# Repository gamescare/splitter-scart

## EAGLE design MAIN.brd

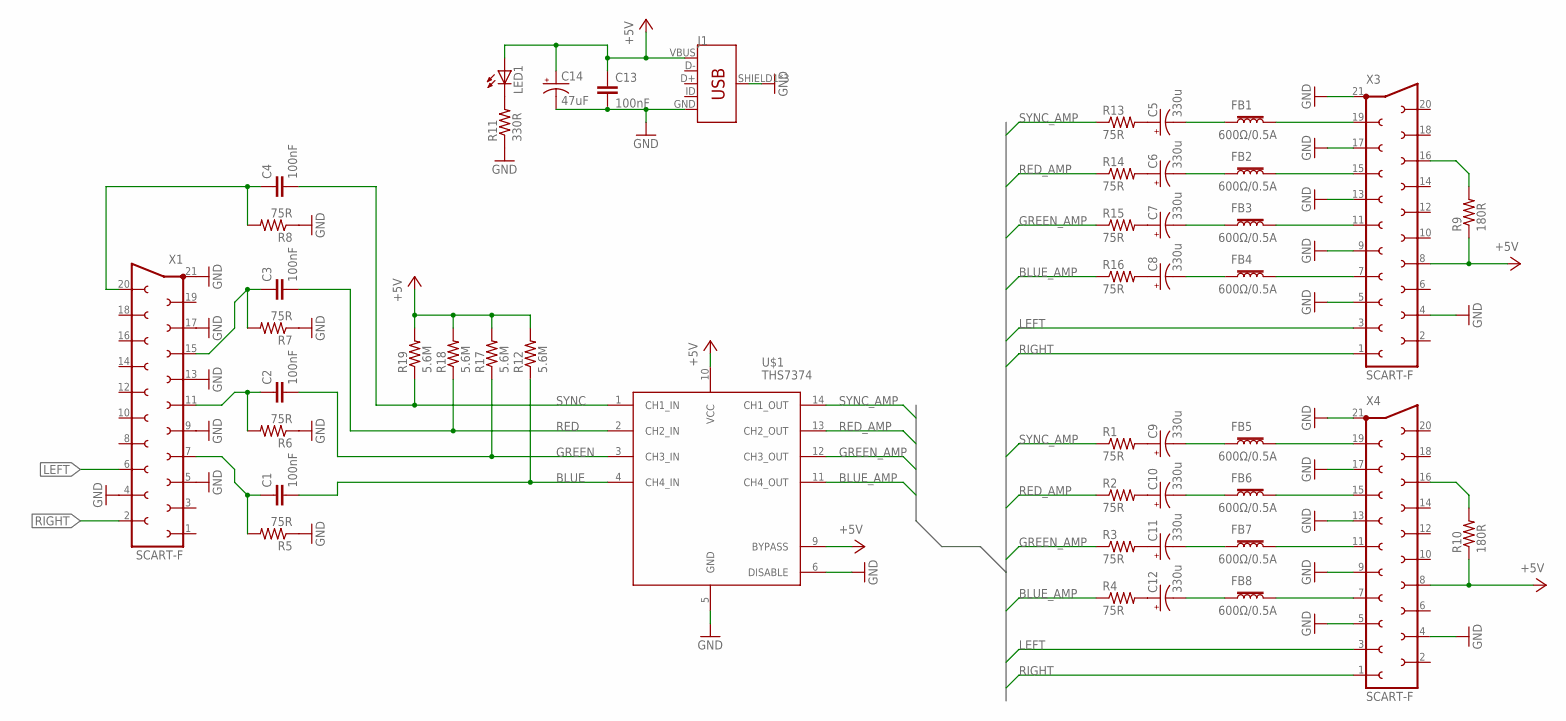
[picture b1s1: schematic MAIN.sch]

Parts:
C1, C2, C3, C4, C13: 100nF; C050-025X075
C5, C6, C7, C8, C9, C10, C11, C12: 330u; E3,5-8
C14: 47uF; E3,5-8
FB1, FB2, FB3, FB4, FB5, FB6, FB7, FB8: 600Ω/0.5A; 0603
J1: USB_MICRO-B_FEMALE-SMT; USB-B-MICRO-SMD
LED1: LED5MM
R1, R2, R3, R4, R5, R6, R7, R8, R13, R14, R15, R16: 75R; 0204/7
R9, R10: 180R; 0204/7
R11: 330R; 0204/7
R12, R17, R18, R19: 5.6M; 0204/7
U$1: THS7374; TSSOP-14
X1, X3, X4: SCART-F

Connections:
+5V: C13.1, C14.+, J1.VBUS, LED1.A, R9.1, R10.1, R12.2, R17.2, R18.2, R19.2, U$1.9 (BYPASS), U$1.10 (VCC), X3.8, X4.8
BLUE: C1.2, R12.1, U$1.4 (CH4_IN)
BLUE_AMP: R4.1, R16.1, U$1.11 (CH4_OUT)
GND: C13.2, C14.-, J1.GND, J1.SHIELD1 (SHIELD), J1.SHIELD2 (SHIELD), J1.SHIELD3 (SHIELD), R5.1, R6.1, R7.1, R8.1, R11.1, U$1.5 (GND), U$1.6 (DISABLE), X1.4, X1.5, X1.9, X1.13, X1.17, X1.21, X3.4, X3.5, X3.9, X3.13, X3.17, X3.21, X4.4, X4.5, X4.9, X4.13, X4.17, X4.21
GREEN: C2.2, R17.1, U$1.3 (CH3_IN)
GREEN_AMP: R3.1, R15.1, U$1.12 (CH3_OUT)
LEFT: X1.6, X3.3, X4.3
unnamed: C9.+, R1.2
unnamed: C10.+, R2.2
unnamed: C11.+, R3.2
unnamed: C12.+, R4.2
unnamed: C5.+, R13.2
unnamed: C6.+, R14.2
unnamed: C7.+, R15.2
unnamed: C8.+, R16.2
unnamed: R10.2, X4.16
unnamed: C1.1, R5.2, X1.7
unnamed: R9.2, X3.16
unnamed: C2.1, R6.2, X1.11
unnamed: C3.1, R7.2, X1.15
unnamed: LED1.K (C), R11.2
unnamed: C4.1, R8.2, X1.20
unnamed: C5.-, FB1.1
unnamed: C6.-, FB2.1
unnamed: C7.-, FB3.1
unnamed: C8.-, FB4.1
unnamed: FB1.2, X3.19
unnamed: FB2.2, X3.15
unnamed: FB3.2, X3.11
unnamed: FB4.2, X3.7
unnamed: FB8.2, X4.7
unnamed: FB7.2, X4.11
unnamed: FB6.2, X4.15
unnamed: FB5.2, X4.19
unnamed: C9.-, FB5.1
unnamed: C10.-, FB6.1
unnamed: C11.-, FB7.1
unnamed: C12.-, FB8.1
RED: C3.2, R18.1, U$1.2 (CH2_IN)
RED_AMP: R2.1, R14.1, U$1.13 (CH2_OUT)
RIGHT: X1.2, X3.1, X4.1
SYNC: C4.2, R19.1, U$1.1 (CH1_IN)
SYNC_AMP: R1.1, R13.1, U$1.14 (CH1_OUT)

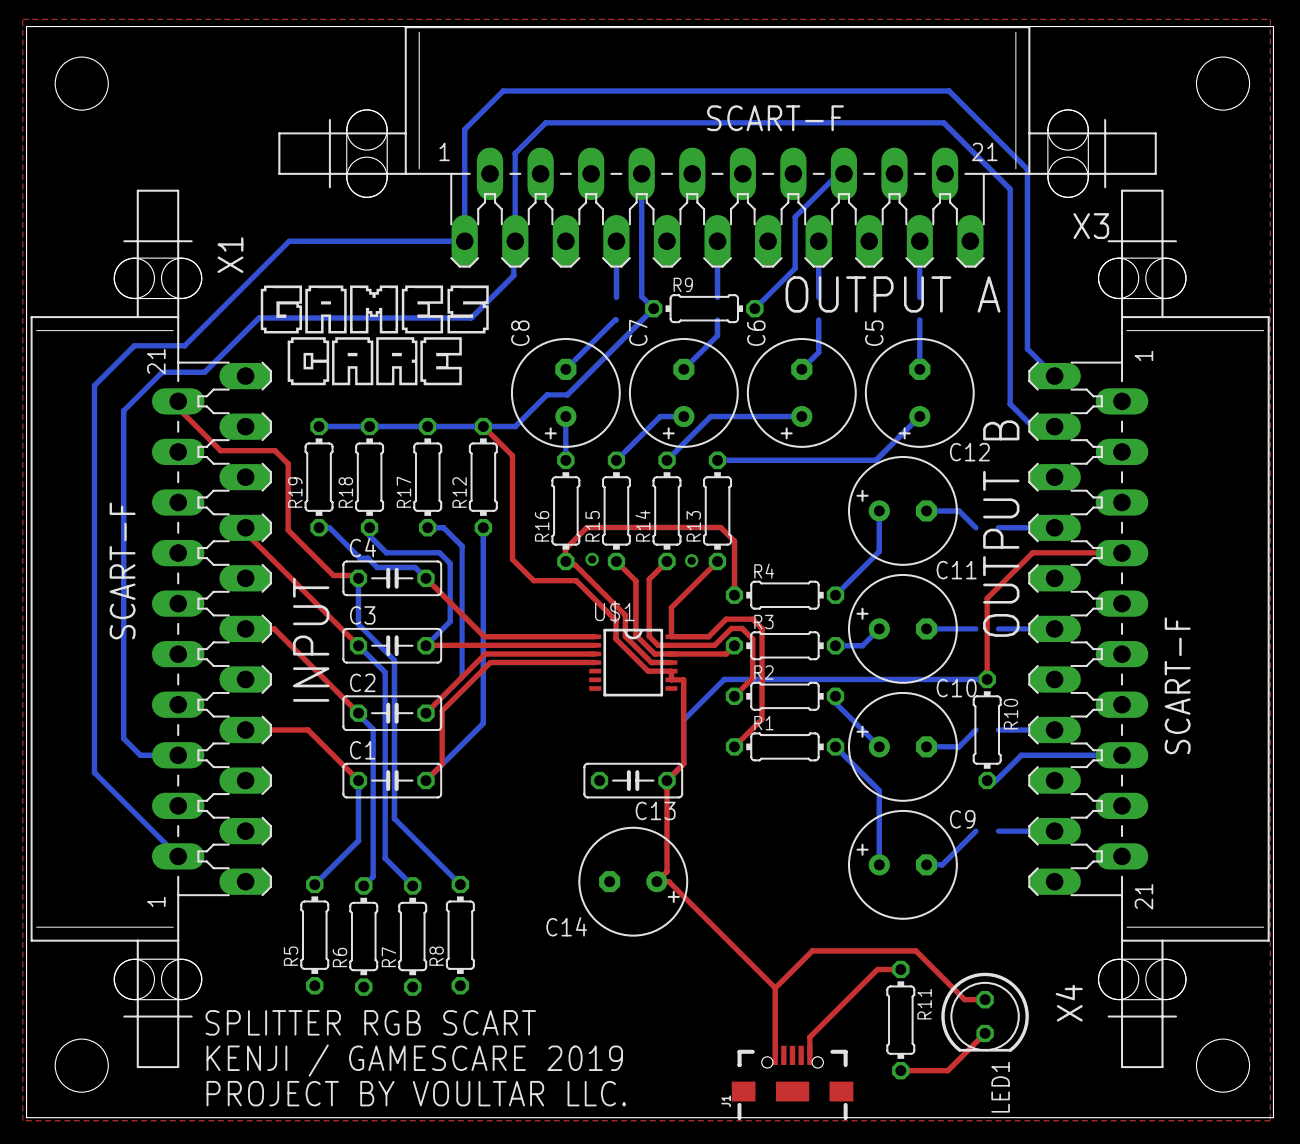
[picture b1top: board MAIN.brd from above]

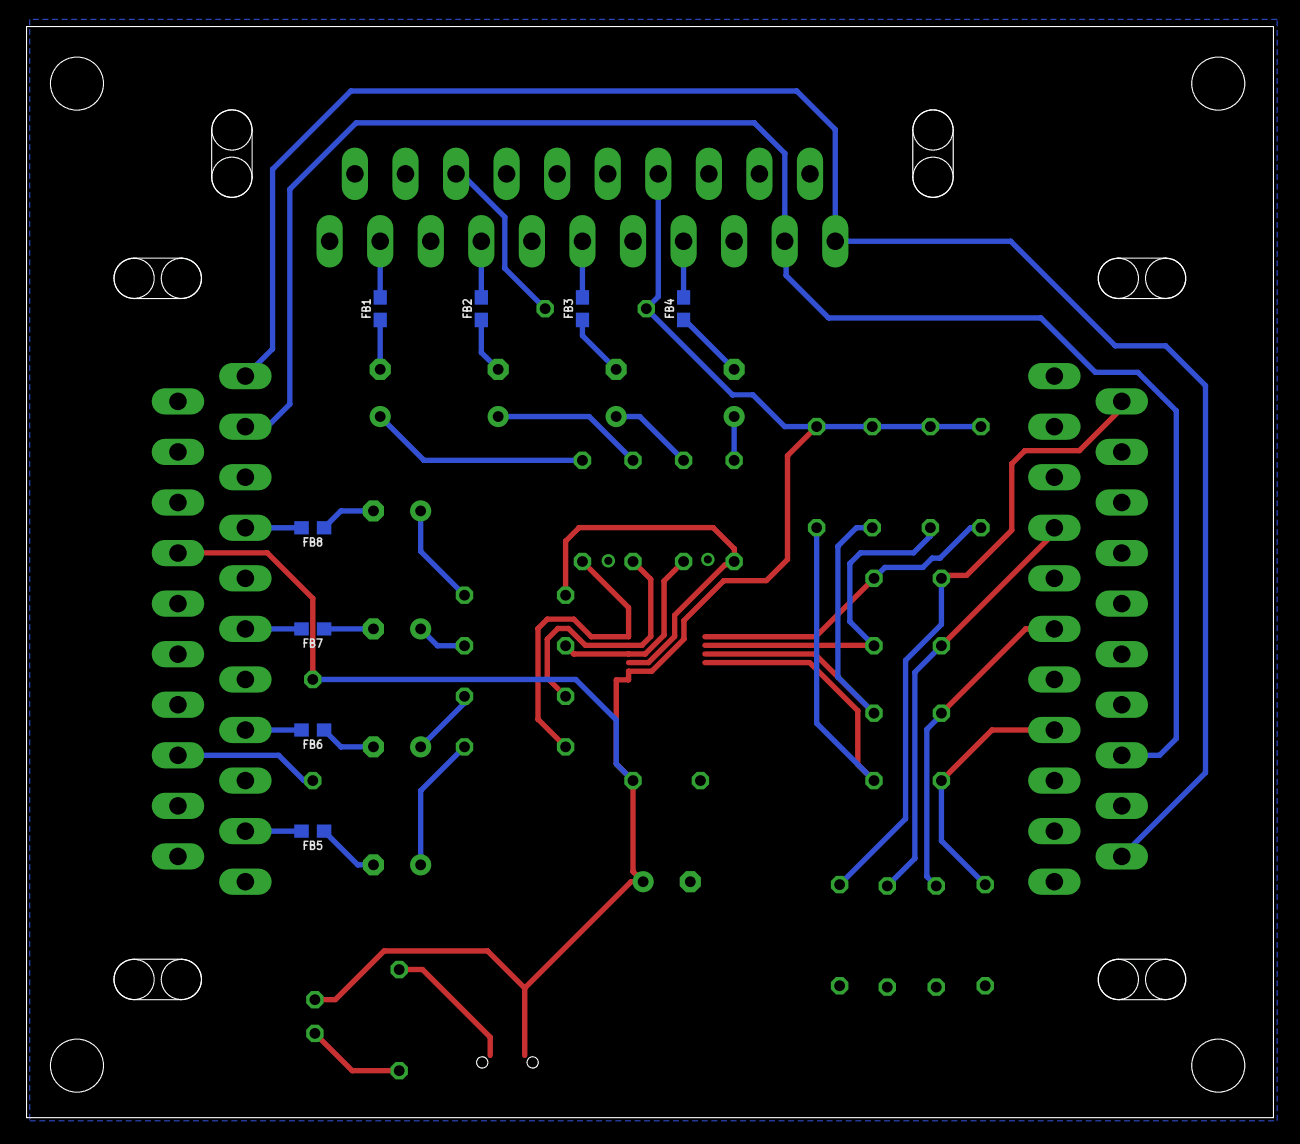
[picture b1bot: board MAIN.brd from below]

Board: 2 copper layers, 94.0 x 82.2 mm, 47 parts (8 on the bottom side), 43 nets.

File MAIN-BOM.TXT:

Partlist exported from C:/Users/eduar/Documents/eagle/SCART SPLITTER/SCART - 2X SCART/MAIN.sch at 29/05/2019 15:09

Part Value          Device            Package      Description                                       MF MPN OC_FARNELL OC_NEWARK PROD_ID    SF_ID     VALUE   
C1   100nF          C-EU050-025X075   C050-025X075 CAPACITOR, European symbol                                                                                 
C2   100nF          C-EU050-025X075   C050-025X075 CAPACITOR, European symbol                                                                                 
C3   100nF          C-EU050-025X075   C050-025X075 CAPACITOR, European symbol                                                                                 
C4   100nF          C-EU050-025X075   C050-025X075 CAPACITOR, European symbol                                                                                 
C5   330u           CPOL-USE3.5-8     E3,5-8       POLARIZED CAPACITOR, American symbol                                                                       
C6   330u           CPOL-USE3.5-8     E3,5-8       POLARIZED CAPACITOR, American symbol                                                                       
C7   330u           CPOL-USE3.5-8     E3,5-8       POLARIZED CAPACITOR, American symbol                                                                       
C8   330u           CPOL-USE3.5-8     E3,5-8       POLARIZED CAPACITOR, American symbol                                                                       
C9   330u           CPOL-USE3.5-8     E3,5-8       POLARIZED CAPACITOR, American symbol                                                                       
C10  330u           CPOL-USE3.5-8     E3,5-8       POLARIZED CAPACITOR, American symbol                                                                       
C11  330u           CPOL-USE3.5-8     E3,5-8       POLARIZED CAPACITOR, American symbol                                                                       
C12  330u           CPOL-USE3.5-8     E3,5-8       POLARIZED CAPACITOR, American symbol                                                                       
C13  100nF          C-EU050-025X075   C050-025X075 CAPACITOR, European symbol                                                                                 
C14  47uF           CPOL-USE3.5-8     E3,5-8       POLARIZED CAPACITOR, American symbol                                                                       
FB1  600O/0.5A      FERRITE_BEAD-0603 0603         Ferrite Bead (blocks, cores, rings, chokes, etc.)                             NDUC-13805           30O/1.8A
FB2  600O/0.5A      FERRITE_BEAD-0603 0603         Ferrite Bead (blocks, cores, rings, chokes, etc.)                             NDUC-13805           30O/1.8A
FB3  600O/0.5A      FERRITE_BEAD-0603 0603         Ferrite Bead (blocks, cores, rings, chokes, etc.)                             NDUC-13805           30O/1.8A
FB4  600O/0.5A      FERRITE_BEAD-0603 0603         Ferrite Bead (blocks, cores, rings, chokes, etc.)                             NDUC-13805           30O/1.8A
FB5  600O/0.5A      FERRITE_BEAD-0603 0603         Ferrite Bead (blocks, cores, rings, chokes, etc.)                             NDUC-13805           30O/1.8A
FB6  600O/0.5A      FERRITE_BEAD-0603 0603         Ferrite Bead (blocks, cores, rings, chokes, etc.)                             NDUC-13805           30O/1.8A
FB7  600O/0.5A      FERRITE_BEAD-0603 0603         Ferrite Bead (blocks, cores, rings, chokes, etc.)                             NDUC-13805           30O/1.8A
FB8  600O/0.5A      FERRITE_BEAD-0603 0603         Ferrite Bead (blocks, cores, rings, chokes, etc.)                             NDUC-13805           30O/1.8A
J1   USB_MINI-B_SMT USB_MINI-B_SMT    USB-MINIB    USB type Mini-B Connector                                                     CONN-08193 PRT-00587         
LED1                LED5MM            LED5MM       LED                                                                                                        
R1   75R            R-US_0204/7       0204/7       RESISTOR, American symbol                                                                                  
R2   75R            R-US_0204/7       0204/7       RESISTOR, American symbol                                                                                  
R3   75R            R-US_0204/7       0204/7       RESISTOR, American symbol                                                                                  
R4   75R            R-US_0204/7       0204/7       RESISTOR, American symbol                                                                                  
R5   75R            R-US_0204/7       0204/7       RESISTOR, American symbol                                                                                  
R6   75R            R-US_0204/7       0204/7       RESISTOR, American symbol                                                                                  
R7   75R            R-US_0204/7       0204/7       RESISTOR, American symbol                                                                                  
R8   75R            R-US_0204/7       0204/7       RESISTOR, American symbol                                                                                  
R9   180R           R-US_0204/7       0204/7       RESISTOR, American symbol                                                                                  
R10  180R           R-US_0204/7       0204/7       RESISTOR, American symbol                                                                                  
R11  330R           R-US_0204/7       0204/7       RESISTOR, American symbol                                                                                  
R12  5.6M           R-US_0204/7       0204/7       RESISTOR, American symbol                                                                                  
R13  75R            R-US_0204/7       0204/7       RESISTOR, American symbol                                                                                  
R14  75R            R-US_0204/7       0204/7       RESISTOR, American symbol                                                                                  
R15  75R            R-US_0204/7       0204/7       RESISTOR, American symbol                                                                                  
R16  75R            R-US_0204/7       0204/7       RESISTOR, American symbol                                                                                  
R17  5.6M           R-US_0204/7       0204/7       RESISTOR, American symbol                                                                                  
R18  5.6M           R-US_0204/7       0204/7       RESISTOR, American symbol                                                                                  
R19  5.6M           R-US_0204/7       0204/7       RESISTOR, American symbol                                                                                  
U$1  THS7374        THS7374           TSSOP-14                                                                                                                
X1   SCART-F        SCART-F           SCART-F      TV SCART CONNECTOR                                       unknown    unknown                                
X3   SCART-F        SCART-F           SCART-F      TV SCART CONNECTOR                                       unknown    unknown                                
X4   SCART-F        SCART-F           SCART-F      TV SCART CONNECTOR                                       unknown    unknown

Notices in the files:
parts and their libraries:
SparkFun-Coils: Licensing: Creative Commons ShareAlike 4.0 International - https://creativecommons.org/licenses/by-sa/4.0
